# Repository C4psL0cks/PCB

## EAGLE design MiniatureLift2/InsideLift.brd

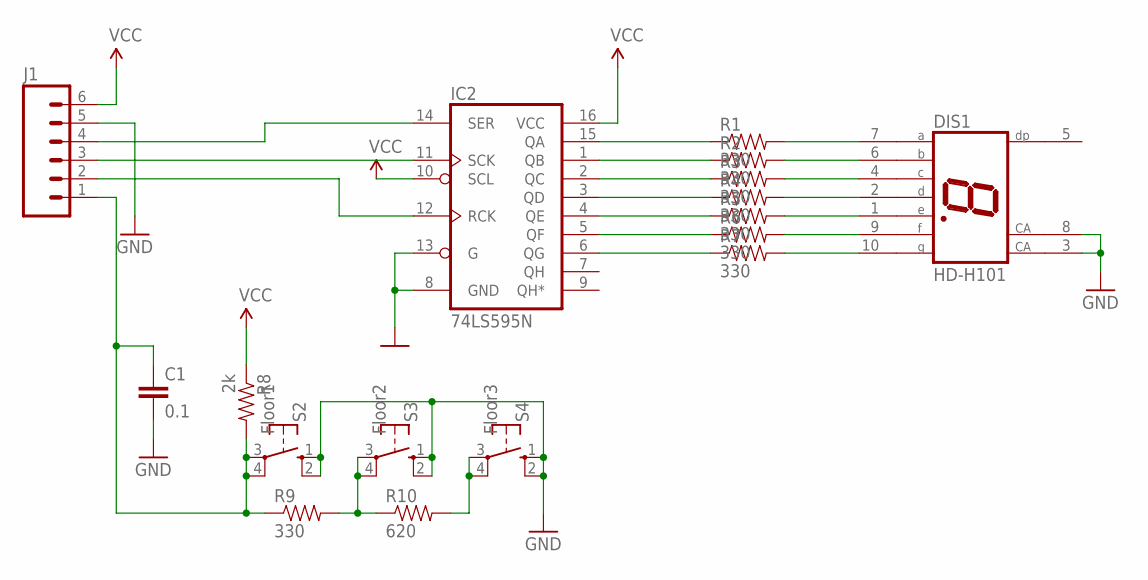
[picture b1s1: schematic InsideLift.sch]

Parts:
C1: 0.1; CAP-PTH-5MM
DIS1: HD-H101; HDSP-M
IC2: 74LS595N; DIL16
J1: M06LONGPADS; 1X06_LONGPADS
R1, R2, R3, R4, R5, R6, R7: 330; AXIAL-0.3
R8: 2k; 0805
R9: 330; 0805
R10: 620; 0805
S2: Floor1; B3F-10XX; MPN B3F-1000
S3: Floor2; B3F-10XX; MPN B3F-1000
S4: Floor3; B3F-10XX; MPN B3F-1000

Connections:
A0: C1.1, J1.1, R8.2, R9.1, S2.3, S2.4 (P1)
GND: C1.2, DIS1.3 (CA), DIS1.8 (CA), IC2.8 (GND), IC2.13 (G), J1.5, S2.1 (S), S2.2 (S1), S3.1 (S), S3.2 (S1), S4.1 (S), S4.2 (S1)
unnamed: IC2.14 (SER), J1.4
unnamed: R9.2, R10.1, S3.3, S3.4 (P1)
unnamed: R10.2, S4.3, S4.4 (P1)
unnamed: IC2.15 (QA), R1.P$1 (1)
unnamed: IC2.1 (QB), R2.P$1 (1)
unnamed: IC2.2 (QC), R3.P$1 (1)
unnamed: IC2.3 (QD), R4.P$1 (1)
unnamed: IC2.4 (QE), R5.P$1 (1)
unnamed: IC2.5 (QF), R6.P$1 (1)
unnamed: IC2.6 (QG), R7.P$1 (1)
unnamed: DIS1.7 (A), R1.P$2 (2)
unnamed: DIS1.6 (B), R2.P$2 (2)
unnamed: DIS1.4 (C), R3.P$2 (2)
unnamed: DIS1.2 (D), R4.P$2 (2)
unnamed: DIS1.1 (E), R5.P$2 (2)
unnamed: DIS1.9 (F), R6.P$2 (2)
unnamed: DIS1.10 (G), R7.P$2 (2)
unnamed: IC2.11 (SCK), J1.3
unnamed: IC2.12 (RCK), J1.2
VCC: IC2.10 (SCL), IC2.16 (VCC), J1.6, R8.1

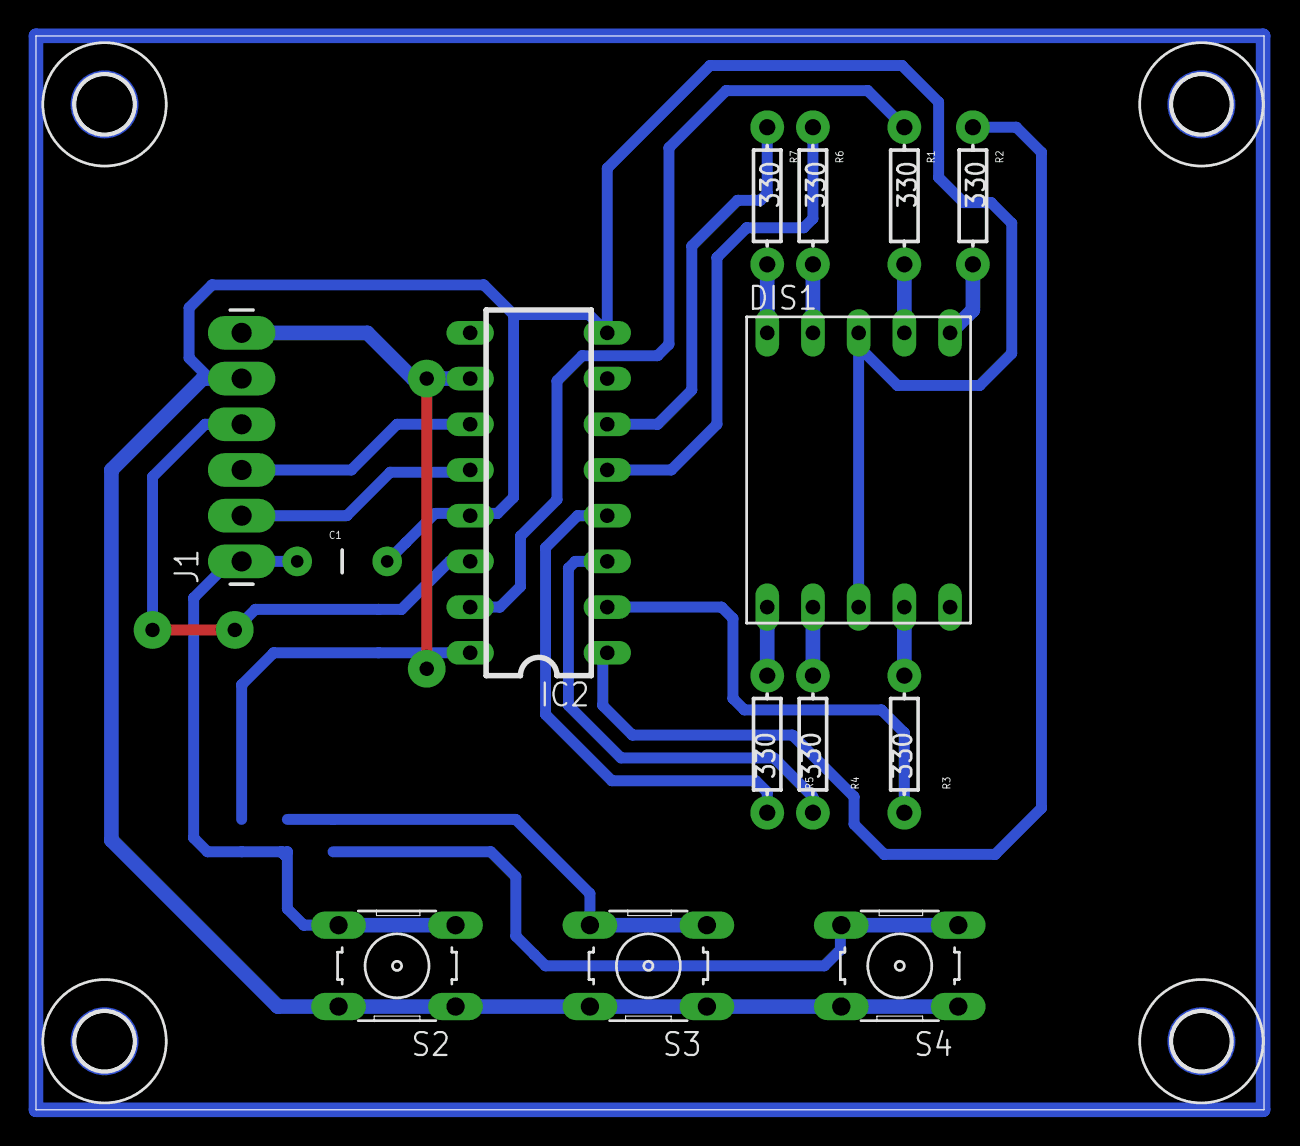
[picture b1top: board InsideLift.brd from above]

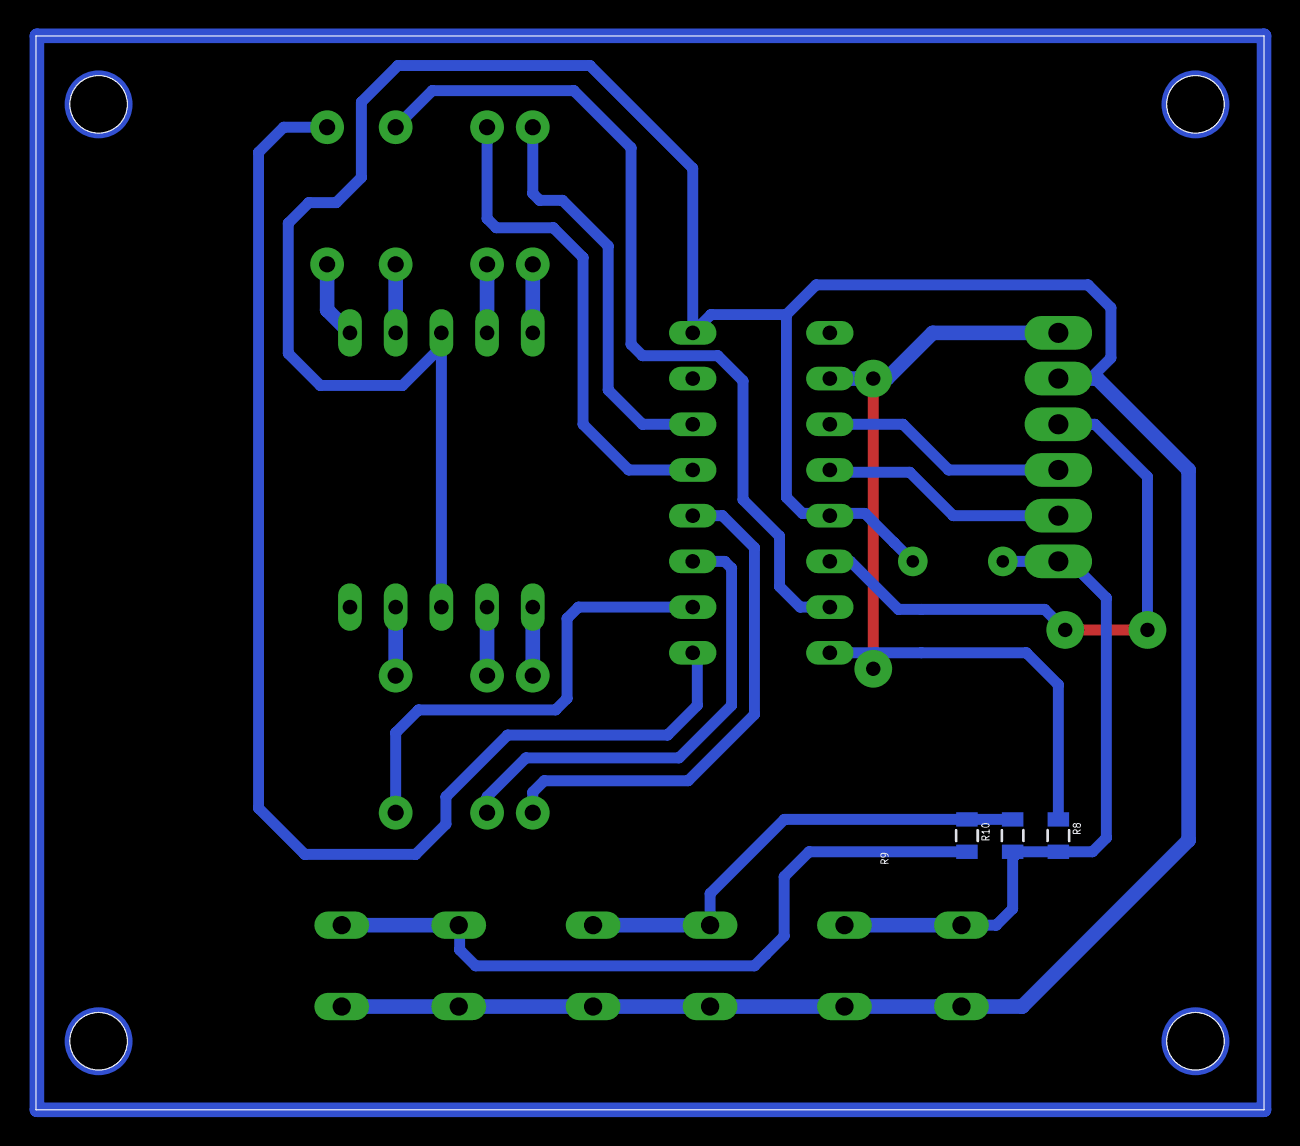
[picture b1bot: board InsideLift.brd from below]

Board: 2 copper layers, 68.2 x 59.7 mm, 21 parts (3 on the bottom side), 22 nets.

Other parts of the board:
U$1, U$2, U$3, U$4: 3,2

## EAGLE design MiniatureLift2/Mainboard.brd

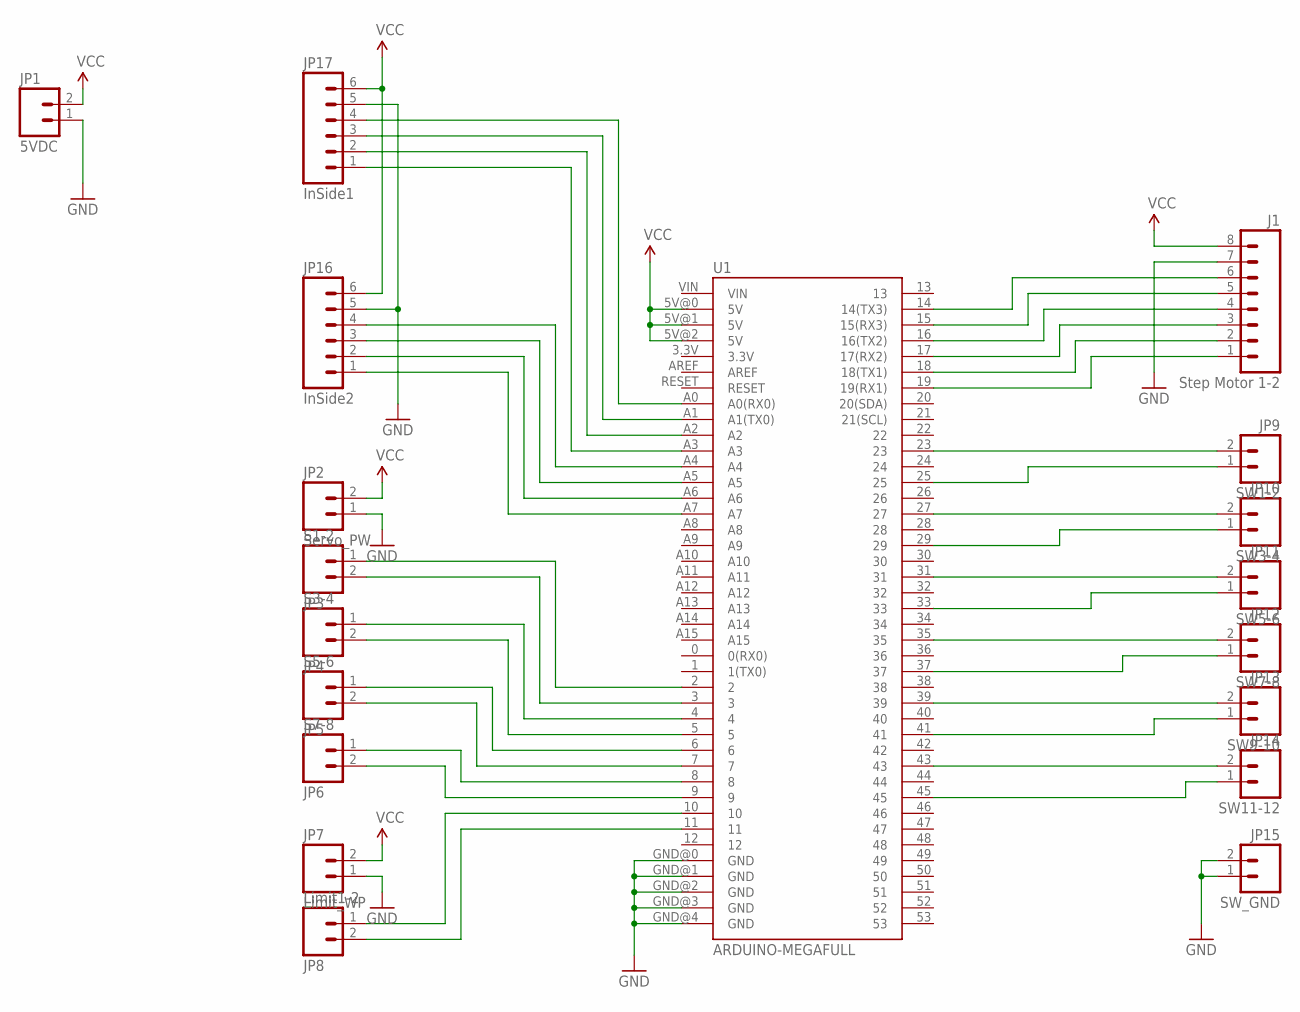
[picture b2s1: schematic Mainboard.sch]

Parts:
J1: Step Motor 1-2; 1X08_LONGPADS
JP1: 5VDC; SCREWTERMINAL-5MM-2
JP2: Servo_PW; SCREWTERMINAL-5MM-2
JP3: S1-2; SCREWTERMINAL-5MM-2
JP4: S3-4; SCREWTERMINAL-5MM-2
JP5: S5-6; SCREWTERMINAL-5MM-2
JP6: S7-8; SCREWTERMINAL-5MM-2
JP7: Limit_WP; SCREWTERMINAL-5MM-2
JP8: Limit1-2; SCREWTERMINAL-5MM-2
JP9: SW1-2; SCREWTERMINAL-5MM-2
JP10: SW3-4; SCREWTERMINAL-5MM-2
JP11: SW5-6; SCREWTERMINAL-5MM-2
JP12: SW7-8; SCREWTERMINAL-5MM-2
JP13: SW9-10; SCREWTERMINAL-5MM-2
JP14: SW11-12; SCREWTERMINAL-5MM-2
JP15: SW_GND; SCREWTERMINAL-5MM-2
JP16: InSide2; 1X06_LONGPADS
JP17: InSide1; 1X06_LONGPADS
U1: ARDUINO-MEGAFULL; ARDUINO_MEGA

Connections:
GND: J1.7, JP1.1, JP2.1, JP7.1, JP15.1, JP15.2, JP16.5, JP17.5, U1.GND@0 (GND), U1.GND@1 (GND), U1.GND@2 (GND), U1.GND@3 (GND), U1.GND@4 (GND)
unnamed: JP3.1, U1.2
unnamed: JP3.2, U1.3
unnamed: JP4.1, U1.4
unnamed: JP4.2, U1.5
unnamed: JP5.1, U1.6
unnamed: JP5.2, U1.7
unnamed: JP6.1, U1.8
unnamed: JP6.2, U1.9
unnamed: JP8.1, U1.10
unnamed: JP8.2, U1.11
unnamed: JP9.2, U1.23
unnamed: JP9.1, U1.25
unnamed: JP10.2, U1.27
unnamed: JP10.1, U1.29
unnamed: JP11.2, U1.31
unnamed: JP11.1, U1.33
unnamed: JP12.2, U1.35
unnamed: JP12.1, U1.37
unnamed: JP13.2, U1.39
unnamed: JP13.1, U1.41
unnamed: JP14.2, U1.43
unnamed: JP14.1, U1.45
unnamed: JP17.4, U1.A0 (A0(RX0))
unnamed: JP17.3, U1.A1 (A1(TX0))
unnamed: JP17.2, U1.A2
unnamed: JP17.1, U1.A3
unnamed: JP16.4, U1.A4
unnamed: JP16.3, U1.A5
unnamed: JP16.2, U1.A6
unnamed: JP16.1, U1.A7
unnamed: J1.1, U1.19 (19(RX1))
unnamed: J1.2, U1.18 (18(TX1))
unnamed: J1.3, U1.17 (17(RX2))
unnamed: J1.4, U1.16 (16(TX2))
unnamed: J1.5, U1.15 (15(RX3))
unnamed: J1.6, U1.14 (14(TX3))
VCC: J1.8, JP1.2, JP2.2, JP7.2, JP16.6, JP17.6, U1.5V@0 (5V), U1.5V@1 (5V), U1.5V@2 (5V)

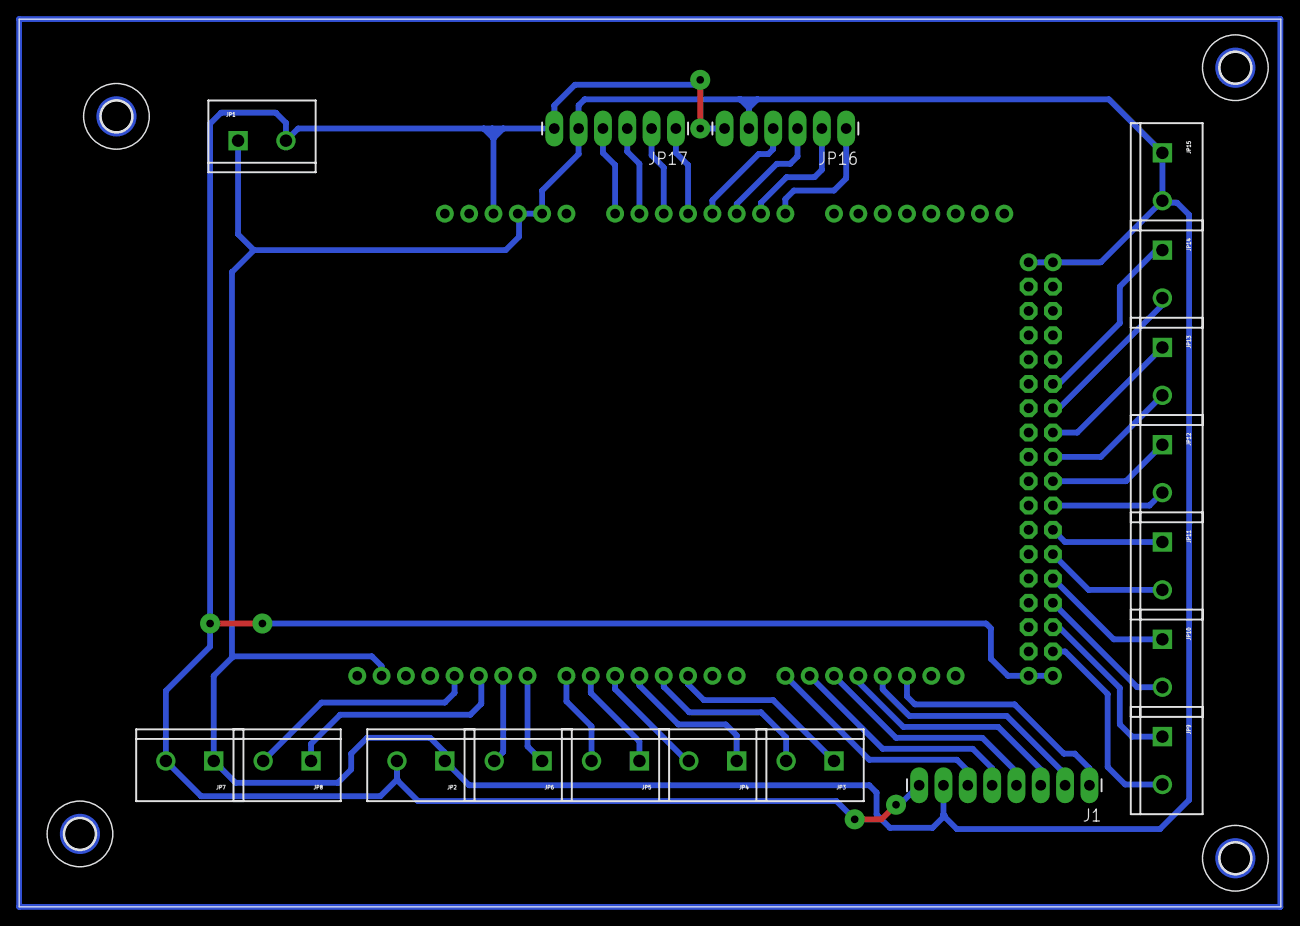
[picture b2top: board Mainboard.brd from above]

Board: 2 copper layers, 131.8 x 92.7 mm, 23 parts (1 on the bottom side), 38 nets.

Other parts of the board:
U$1, U$2, U$3, U$4: 3,2

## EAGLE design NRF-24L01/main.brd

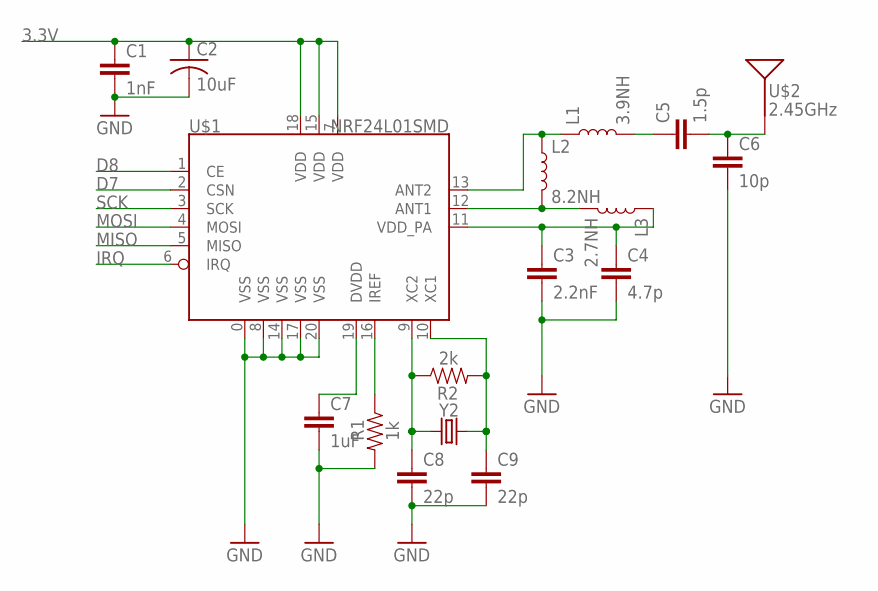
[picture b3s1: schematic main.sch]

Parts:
C1: 1nF; 0805
C2: 10uF; C1206
C3: 2.2nF; 0805
C4: 4.7p; 0805
C5: 1.5p; 0805
C6: 10p; 0805
C7: 1uF; 0805
C8, C9: 22p; 0805
L1: 3.9NH; 0402
L2: 8.2NH; 0402
L3: 2.7NH; 0402
R1: 1k; 0805
R2: 2k; 0805
U$1: NRF24L01SMD; QFN20-4X4MM
U$2: 2.45GHz; ANT-2.4GHZ-6.5X2.2MM
Y2: CRYSTALSMD-5X3.2-4PAD; CRYSTAL-SMD-5X3.2-4PAD

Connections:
3.3V: C1.1, C2.1, U$1.7 (VDD), U$1.15 (VDD), U$1.18 (VDD)
D7: U$1.2 (CSN)
D8: U$1.1 (CE)
GND: C1.2, C2.2, C3.2, C4.2, C6.2, C7.2, C8.2, C9.2, R1.2, U$1.0 (VSS), U$1.8 (VSS), U$1.14 (VSS), U$1.17 (VSS), U$1.20 (VSS)
IRQ: U$1.6 (IRQ)
MISO: U$1.5 (MISO)
MOSI: U$1.4 (MOSI)
unnamed: C5.1, L1.2
unnamed: L1.1, L2.1, U$1.13 (ANT2)
unnamed: L2.2, L3.2, U$1.12 (ANT1)
unnamed: C3.1, C4.1, L3.1, U$1.11 (VDD_PA)
unnamed: C7.1, U$1.19 (DVDD)
unnamed: R1.1, U$1.16 (IREF)
unnamed: C5.2, C6.1, U$2.FEED
unnamed: C8.1, R2.1, U$1.9 (XC2), Y2.1
unnamed: C9.1, R2.2, U$1.10 (XC1), Y2.3 (2)
SCK: U$1.3 (SCK)

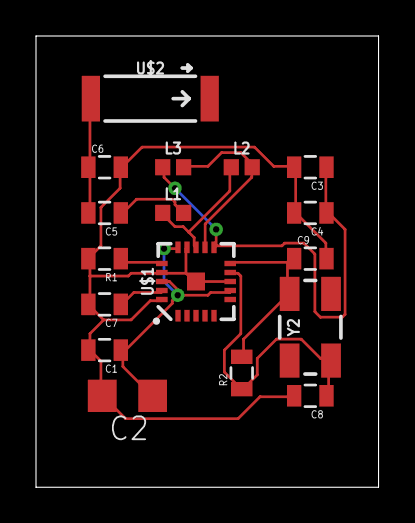
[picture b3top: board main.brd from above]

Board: 2 copper layers, 19.0 x 25.1 mm, 17 parts (0 on the bottom side), 11 nets.

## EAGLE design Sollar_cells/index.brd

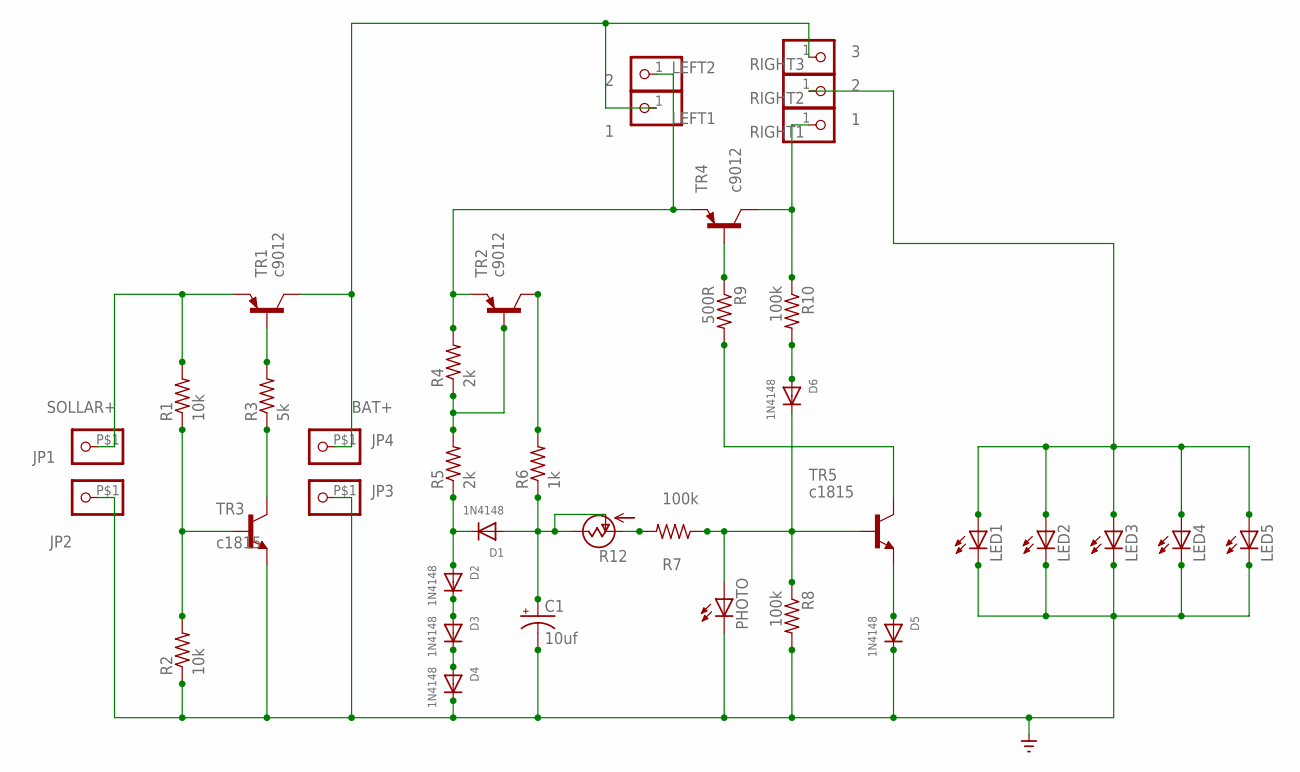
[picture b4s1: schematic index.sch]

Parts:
C1: 10uf; CPOL-RADIAL-10UF-25V
D1, D2, D3, D4, D5, D6: 1N4148; DO-1N4148
JP1, JP2, JP3, JP4: PINHD-1X1-BIGPOGO; 1X1-BIGPOGO
LED1, LED2, LED3, LED4, LED5: LED3MM
LEFT1: 1; 1X01-CLEANBIG
LEFT2: 2; 1X01-CLEANBIG
PHOTO: LED3MM
R1, R2: 10k; 0207/9
R3: 5k; 0207/9
R4, R5: 2k; 0207/9
R6: 1k; 0207/9
R7, R8, R10: 100k; 0207/9
R9: 500R; 0207/9
R12: POTTRECP10S; ECP10S
RIGHT1: 1; 1X01-CLEANBIG
RIGHT2: 2; 1X01-CLEANBIG
RIGHT3: 3; 1X01-CLEANBIG
TR1, TR2, TR4: c9012; TO92-EBC-OVAL
TR3, TR5: c1815; TO92-ECB

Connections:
BAT+: JP4.P$1, LEFT1.1, RIGHT3.1, TR1.C
GND: C1.2 (-), D4.C, D5.C, JP2.P$1, JP3.P$1, LED1.K (C), LED2.K (C), LED3.K (C), LED4.K (C), LED5.K (C), PHOTO.K (C), R2.1, R8.2, TR3.E
unnamed: R1.1, R2.2, TR3.B
unnamed: R3.1, TR3.C
unnamed: R3.2, TR1.B
unnamed: D1.C, D2.A, R5.1
unnamed: D2.C, D3.A
unnamed: D3.C, D4.A
unnamed: LEFT2.1, R4.2, TR2.E, TR4.E
unnamed: R4.1, R5.2, TR2.B
unnamed: R6.2, TR2.C
unnamed: C1.1 (+), D1.A, R6.1, R12.E (VSS), R12.S (OUT)
unnamed: D6.C, PHOTO.A, R7.1, R8.1, TR5.B
unnamed: D5.A, TR5.E
unnamed: R9.2, TR5.C
unnamed: R9.1, TR4.B
unnamed: R10.1, RIGHT1.1, TR4.C
unnamed: D6.A, R10.2
unnamed: R7.2, R12.A (VDD)
unnamed: LED1.A, LED2.A, LED3.A, LED4.A, LED5.A, RIGHT2.1
SOLLAR+: JP1.P$1, R1.2, TR1.E

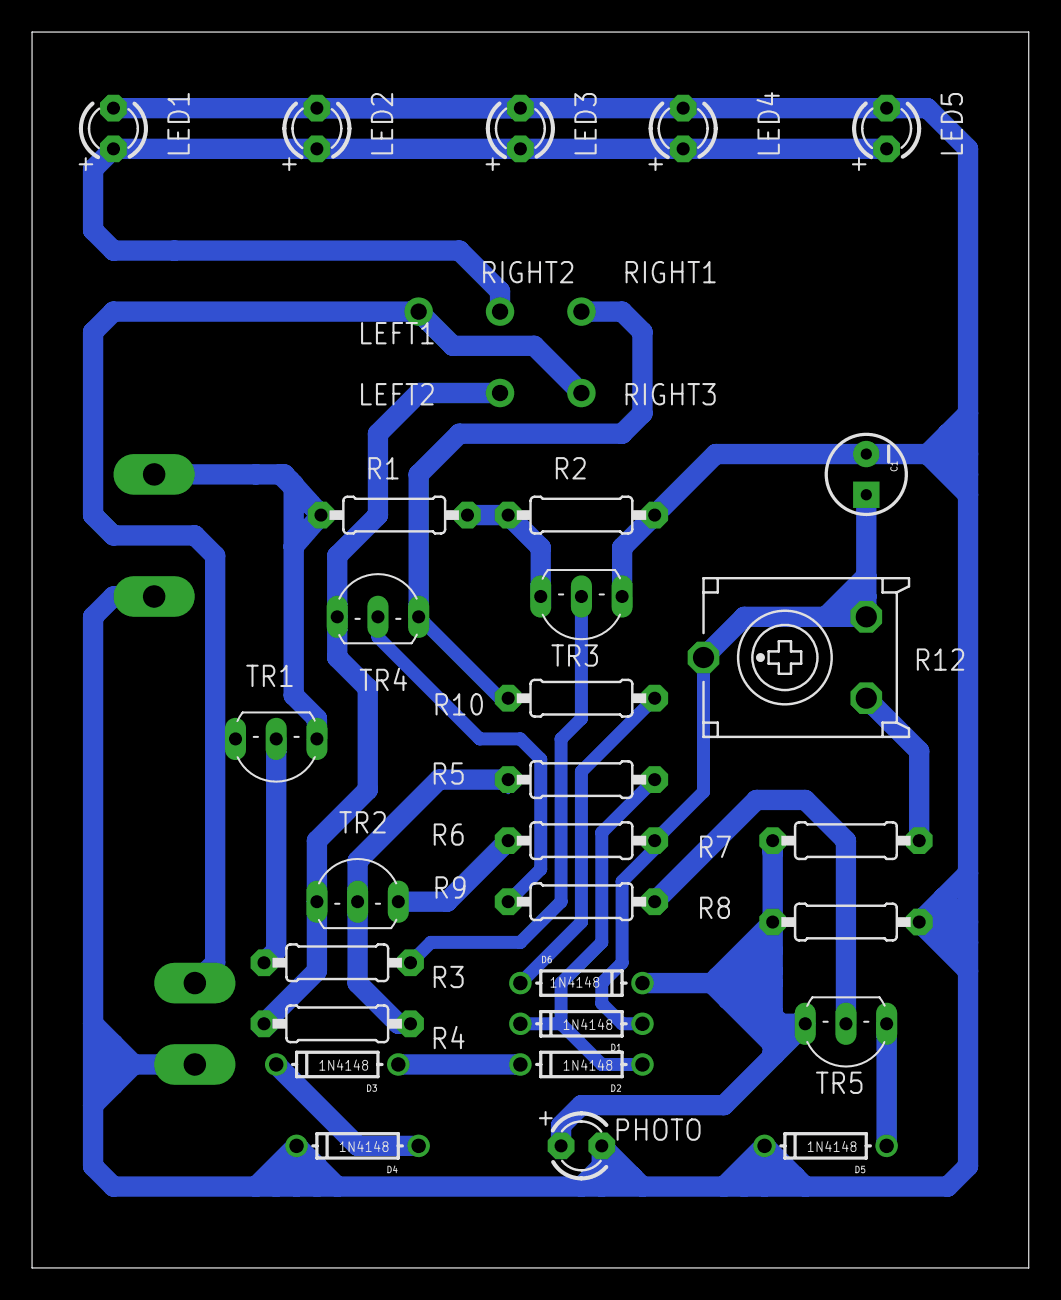
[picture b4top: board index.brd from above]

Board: 2 copper layers, 62.2 x 77.1 mm, 38 parts (0 on the bottom side), 21 nets.

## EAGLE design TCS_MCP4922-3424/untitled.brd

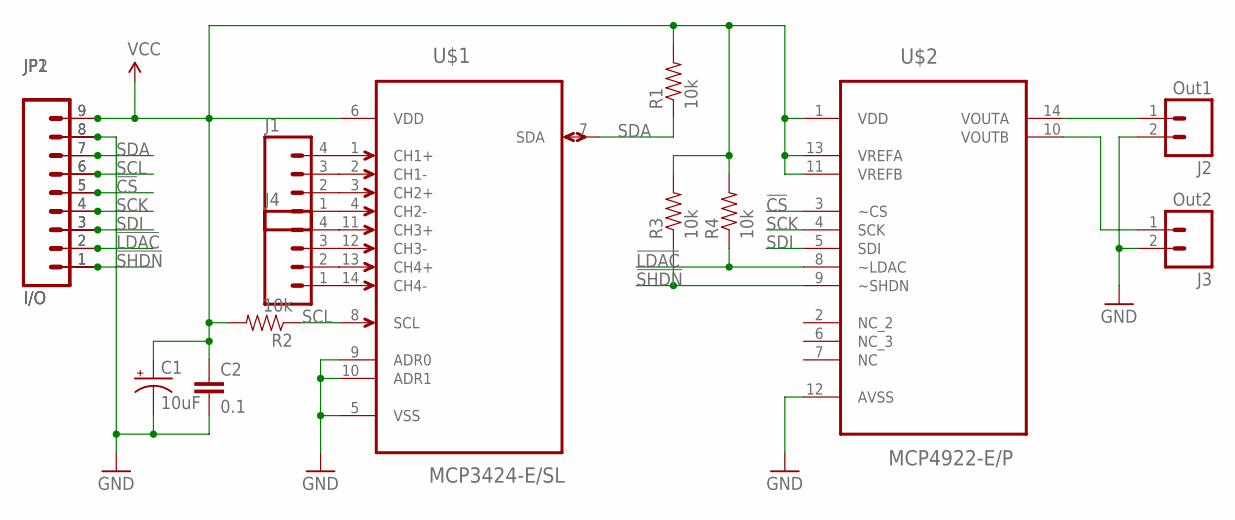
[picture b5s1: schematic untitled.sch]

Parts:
C1: 10uF; CPOL-RADIAL-10UF-25V
C2: 0.1; CAP-PTH-5MM
J1, J4: M04LONGPADS; 1X04_LONGPADS
J2: Out1; 1X02_LONGPADS
J3: Out2; 1X02_LONGPADS
JP1, JP2: I/O; 1X09_LONGPADS
R1, R2, R3, R4: 10k; AXIAL-0.3
U$1: MCP3424-E/SL; SOIC127P600X175-14N
U$2: MCP4922-E/P; DIP254P762X533-14

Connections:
!CS: JP1.5, JP2.5, U$2.3 (~CS)
!LDAC: JP1.2, JP2.2, R4.P$1 (1), U$2.8 (~LDAC)
!SHDN: JP1.1, JP2.1, R3.P$1 (1), U$2.9 (~SHDN)
GND: C1.2 (-), C2.2, J2.2, J3.2, JP1.8, JP2.8, U$1.5 (VSS), U$1.9 (ADR0), U$1.10 (ADR1), U$2.12 (AVSS)
unnamed: J1.1, U$1.4 (CH2-)
unnamed: J1.2, U$1.3 (CH2+)
unnamed: J1.3, U$1.2 (CH1-)
unnamed: J1.4, U$1.1 (CH1+)
unnamed: J4.1, U$1.14 (CH4-)
unnamed: J4.2, U$1.13 (CH4+)
unnamed: J4.3, U$1.12 (CH3-)
unnamed: J4.4, U$1.11 (CH3+)
unnamed: J2.1, U$2.14 (VOUTA)
unnamed: J3.1, U$2.10 (VOUTB)
SCK: JP1.4, JP2.4, U$2.4 (SCK)
SCL: JP1.6, JP2.6, R2.P$1 (1), U$1.8 (SCL)
SDA: JP1.7, JP2.7, R1.P$1 (1), U$1.7 (SDA)
SDI: JP1.3, JP2.3, U$2.5 (SDI)
VCC: C1.1 (+), C2.1, JP1.9, JP2.9, R1.P$2 (2), R2.P$2 (2), R3.P$2 (2), R4.P$2 (2), U$1.6 (VDD), U$2.1 (VDD), U$2.11 (VREFB), U$2.13 (VREFA)

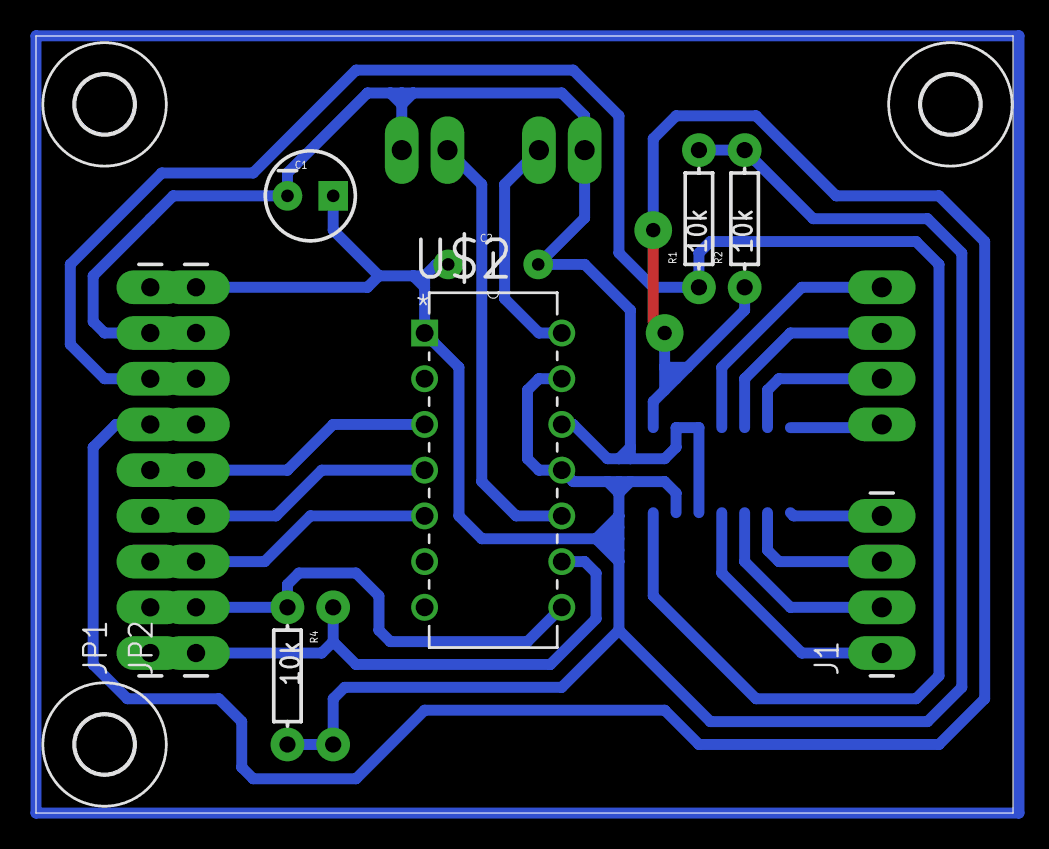
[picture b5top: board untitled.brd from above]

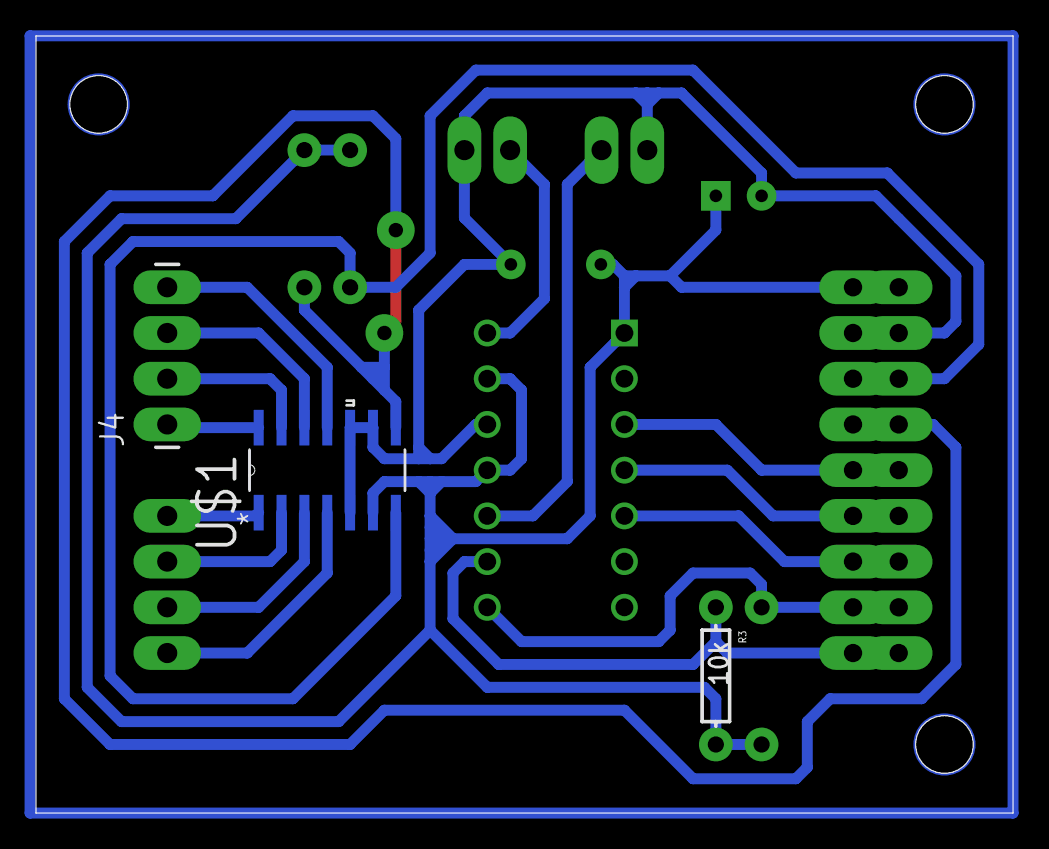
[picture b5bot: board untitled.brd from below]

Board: 2 copper layers, 54.3 x 43.2 mm, 17 parts (3 on the bottom side), 19 nets.

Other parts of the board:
U$3, U$4, U$5: 3,2

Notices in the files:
parts and their libraries:
SparkFun-DigitalIC: Licensing: Creative Commons ShareAlike 4.0 International - https://creativecommons.org/licenses/by-sa/4.0
SparkFun: Licensing: CC v3.0 Share-Alike You are welcome to use this library for commercial purposes.
